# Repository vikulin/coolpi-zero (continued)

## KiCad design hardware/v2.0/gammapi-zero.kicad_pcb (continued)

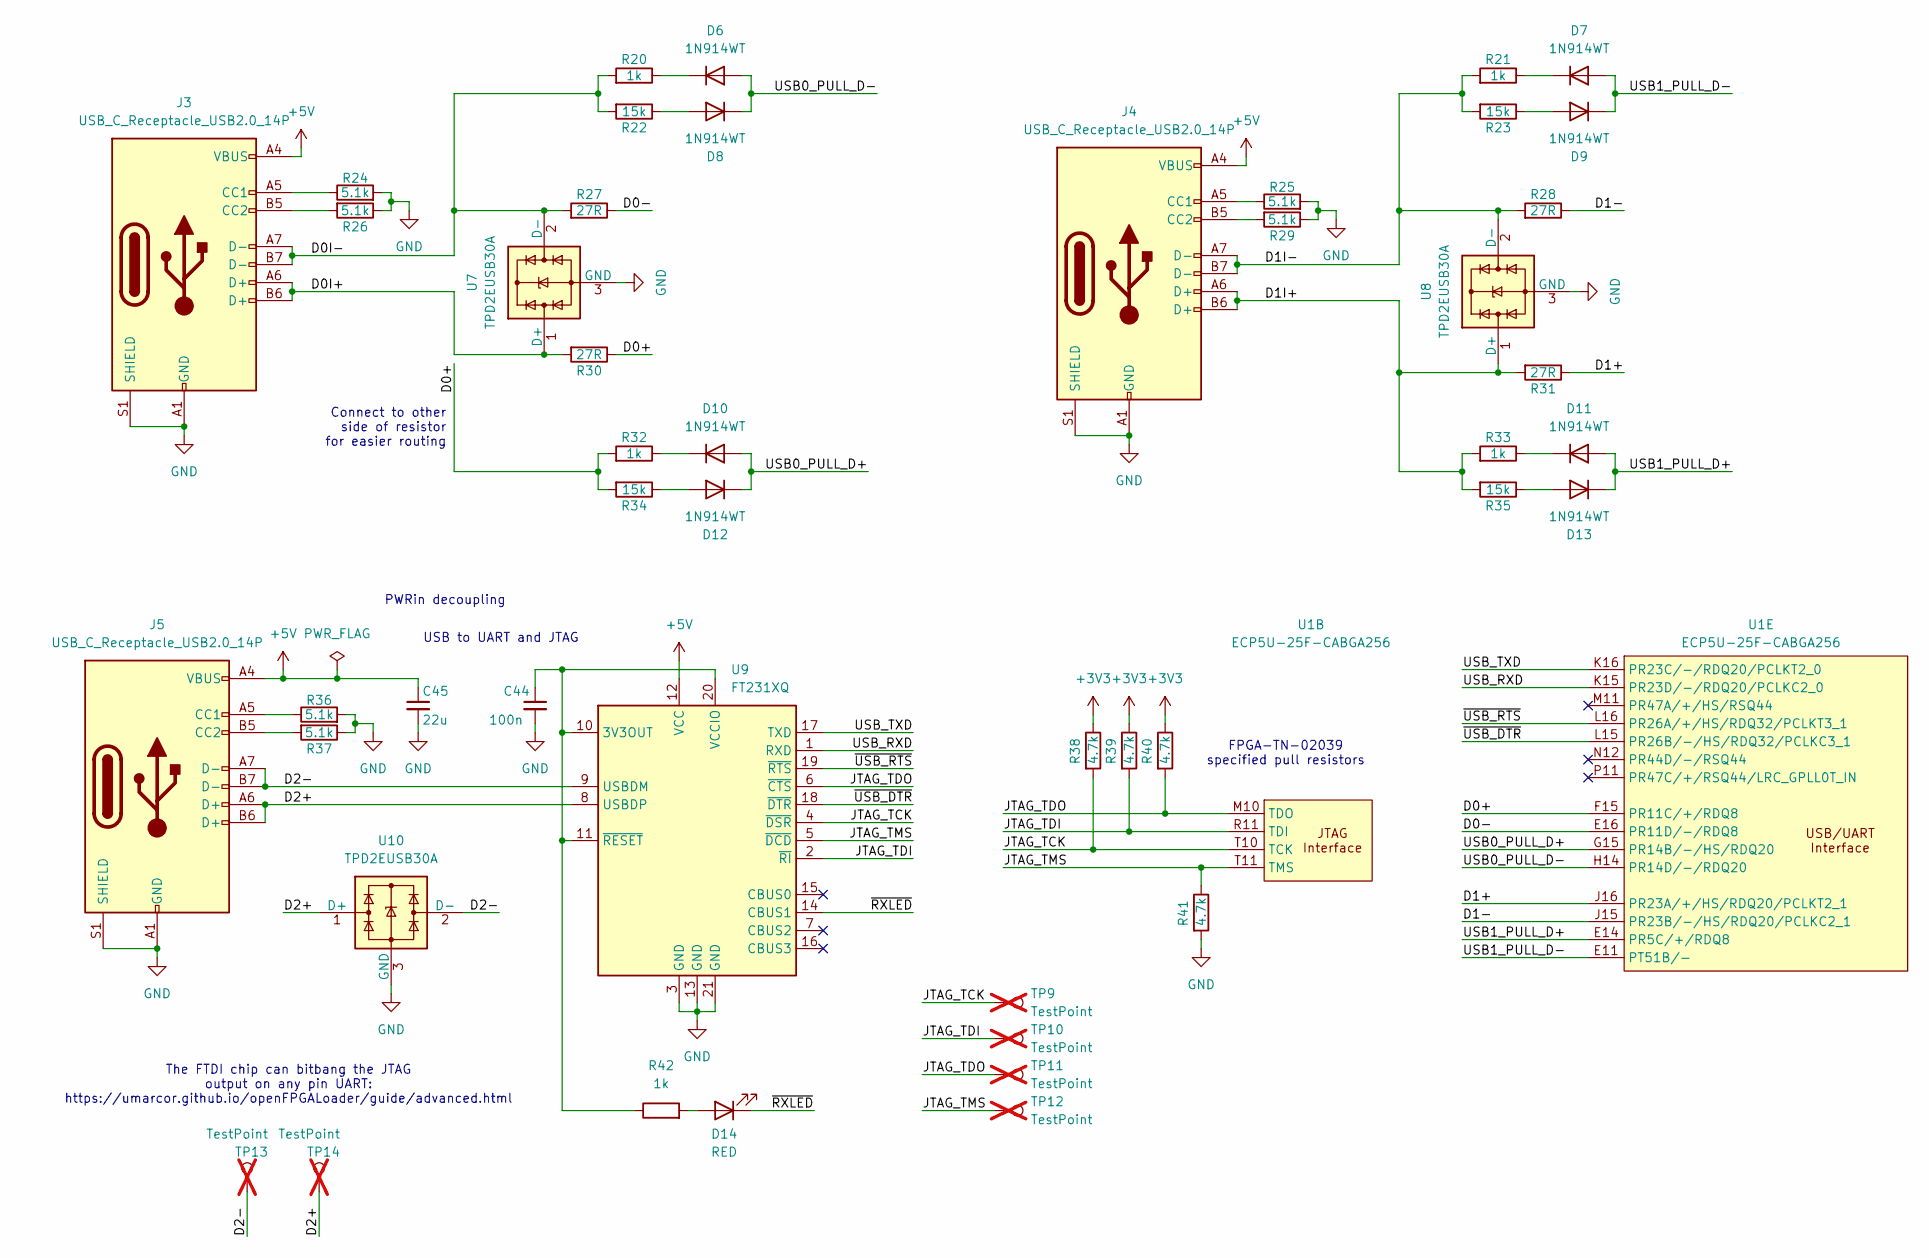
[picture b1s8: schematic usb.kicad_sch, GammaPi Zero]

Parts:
C44: 100n; C_0402_1005Metric; Manufactuer Part Number CL05B104KB54PNC; LCSC Part # C307331
C45: 22u; C_0603_1608Metric; Manufactuer Part Number CL10A226MQ8NRNC; LCSC Part # C59461
D6, D7, D8, D9, D10, D11, D12, D13: 1N914WT; D_SOD-523; Manufactuer Part Number 1N914WT; LCSC Part # C2836064
D14: RED; LED_0603_1608Metric; Manufactuer Part Number KT-0603R; LCSC Part # C2286
J3, J4, J5: USB_C_Receptacle_USB2.0_14P; USB_C_Receptacle_GCT_USB4105-xx-A_16P_TopMnt_Horizontal; Manufactuer Part Number TYPE-C 16PIN 2MD(073); LCSC Part # C2765186
R20, R21, R32, R33, R42: 1k; R_0402_1005Metric; Manufactuer Part Number 0402WGF1001TCE; LCSC Part # C11702
R22, R23, R34, R35: 15k; R_0402_1005Metric; Manufactuer Part Number 0402WGF1502TCE; LCSC Part # C25756
R24, R25, R26, R29, R36, R37: 5.1k; R_0402_1005Metric; Manufactuer Part Number 0402WGF5101TCE; LCSC Part # C25905
R27, R28, R30, R31: 27R; R_0201_0603Metric; Manufactuer Part Number 0201WMF270JTEE; LCSC Part # C473051
R38, R39, R40, R41: 4.7k; R_0402_1005Metric; Manufactuer Part Number 0402WGF4701TCE; LCSC Part # C25900
TP9, TP10, TP11, TP12: TestPoint; TestPoint_Pad_D1.0mm_Blank; not fitted
TP13, TP14: TestPoint; TestPoint_Pad_D2.0mm_Blank; not fitted
U1: ECP5U-25F-CABGA256; BGA-256_14.0x14.0mm_Layout16x16_P0.8mm_Ball0.45mm_Pad0.32mm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; MANUFACTURER_PART_NUMBER LFE5U-25F-6BG256C; LCSC Part # C1521614
U7, U8, U10: TPD2EUSB30A; Texas_DRT-3; Manufactuer Part Number TPD2EUSB30ADRTR; LCSC Part # C3011197
U9: FT231XQ; QFN-20-1EP_4x4mm_P0.5mm_EP2.5x2.5mm; Manufactuer Part Number FT231XQ-R; LCSC Part # C132159

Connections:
+3V3: R38.1, R39.1, R40.1; also elsewhere on the board
+5V: C45.1, J3.A4 (VBUS), J3.A9 (VBUS), J3.B4 (VBUS), J3.B9 (VBUS), J4.A4 (VBUS), J4.A9 (VBUS), J4.B4 (VBUS), J4.B9 (VBUS), J5.A4 (VBUS), J5.A9 (VBUS), J5.B4 (VBUS), J5.B9 (VBUS), U9.12 (VCC); also elsewhere on the board
/USB/D0+: R30.1, R32.2, R34.2, U1.F15 (PR11C/+/RDQ8)
/USB/D0-: R27.1, U1.E16 (PR11D/-/RDQ8)
/USB/D0I+: J3.A6 (D+), J3.B6 (D+), R30.2, U7.1 (D+)
/USB/D0I-: J3.A7 (D-), J3.B7 (D-), R20.2, R22.2, R27.2, U7.2 (D-)
/USB/D1+: R31.1, U1.J16 (PR23A/+/HS/RDQ20/PCLKT2_1)
/USB/D1-: R28.1, U1.J15 (PR23B/-/HS/RDQ20/PCLKC2_1)
/USB/D1I+: J4.A6 (D+), J4.B6 (D+), R31.2, R33.2, R35.2, U8.1 (D+)
/USB/D1I-: J4.A7 (D-), J4.B7 (D-), R21.2, R23.2, R28.2, U8.2 (D-)
/USB/D2+: J5.A6 (D+), J5.B6 (D+), TP14.1, U9.8 (USBDP), U10.1 (D+)
/USB/D2-: J5.A7 (D-), J5.B7 (D-), TP13.1, U9.9 (USBDM), U10.2 (D-)
/USB/JTAG_TCK: R38.2, TP9.1, U1.T10 (TCK), U9.4 (~DSR)
/USB/JTAG_TDI: R39.2, TP10.1, U1.R11 (TDI), U9.2 (~RI)
/USB/JTAG_TDO: R40.2, TP11.1, U1.M10 (TDO), U9.6 (~CTS)
/USB/JTAG_TMS: R41.1, TP12.1, U1.T11 (TMS), U9.5 (~DCD)
/USB/USB0_PULL_D+: D10.2 (A), D12.1 (K), U1.G15 (PR14B/-/HS/RDQ20)
/USB/USB0_PULL_D-: D6.2 (A), D8.1 (K), U1.H14 (PR14D/-/RDQ20)
/USB/USB1_PULL_D+: D11.2 (A), D13.1 (K), U1.E14 (PR5C/+/RDQ8)
/USB/USB1_PULL_D-: D7.2 (A), D9.1 (K), U1.E11 (PT51B/-)
/USB/USB_RXD: U1.K15 (PR23D/-/RDQ20/PCLKC2_0), U9.1 (RXD)
/USB/USB_TXD: U1.K16 (PR23C/-/RDQ20/PCLKT2_0), U9.17 (TXD)
/USB/~RXLED: D14.1 (K), U9.14 (CBUS1)
/USB/~USB_DTR: U1.L15 (PR26B/-/HS/RDQ32/PCLKC3_1), U9.18 (~DTR)
/USB/~USB_RTS: U1.L16 (PR26A/+/HS/RDQ32/PCLKT3_1), U9.19 (~RTS)
GND: C44.2, C45.2, J3.A1 (GND), J3.A12 (GND), J3.B1 (GND), J3.B12 (GND), J3.S1 (SHIELD), J4.A1 (GND), J4.A12 (GND), J4.B1 (GND), J4.B12 (GND), J4.S1 (SHIELD), J5.A1 (GND), J5.A12 (GND), J5.B1 (GND), J5.B12 (GND), J5.S1 (SHIELD), R24.2, R25.2, R26.1, R29.1, R36.2, R37.1, R41.2, U7.3 (GND), U8.3 (GND), U9.3 (GND), U9.13 (GND), U9.21 (GND), U10.3 (GND); also elsewhere on the board
unnamed: D6.1 (K), R20.1
unnamed: D7.1 (K), R21.1
unnamed: D8.2 (A), R22.1
unnamed: D9.2 (A), R23.1
unnamed: D10.1 (K), R32.1
unnamed: D11.1 (K), R33.1
unnamed: D12.2 (A), R34.1
unnamed: D13.2 (A), R35.1
unnamed: D14.2 (A), R42.2
unnamed: J3.A5 (CC1), R24.1
unnamed: J3.B5 (CC2), R26.2
unnamed: J4.A5 (CC1), R25.1
unnamed: J4.B5 (CC2), R29.2
unnamed: J5.A5 (CC1), R36.1
unnamed: J5.B5 (CC2), R37.2
unnamed: C44.1, R42.1, U9.10 (3V3OUT), U9.11 (~RESET), U9.20 (VCCIO)

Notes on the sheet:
PWRin decoupling
FPGA-TN-02039 specified pull resistors
USB to UART and JTAG
The FTDI chip can bitbang the JTAG output on any pin UART: https://umarcor.github.io/openFPGALoader/guide/advanced.html
Connect to other side of resistor for easier routing

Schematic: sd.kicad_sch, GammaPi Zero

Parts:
C54: 10u; C_0603_1608Metric; Manufactuer Part Number CL10A106KP8NNNC; LCSC Part # C19702
J6: Micro_SD_Card_Det2; microSD_HC_SOFNG_TF-008; Manufactuer Part Number TF-008; LCSC Part # C428465
U1: ECP5U-25F-CABGA256; BGA-256_14.0x14.0mm_Layout16x16_P0.8mm_Ball0.45mm_Pad0.32mm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; MANUFACTURER_PART_NUMBER LFE5U-25F-6BG256C; LCSC Part # C1521614

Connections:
+3V3: C54.1, J6.4 (VDD); also elsewhere on the board
/uSD/SD_CLK: J6.5 (CLK), U1.P15 (PR32B/-/HS/RDQSN32)
/uSD/SD_CMD: J6.3 (CMD), U1.N16 (PR32A/+/HS/RDQS32)
/uSD/SD_DAT0: J6.7 (DAT0), U1.P14 (PR38B/-/HS/RDQ44)
/uSD/SD_DAT1: J6.8 (DAT1), U1.R14 (PR41B/-/HS/RDQ44)
/uSD/SD_DAT2: J6.1 (DAT2), U1.M15 (PR26D/-/RDQ32/PCLKC3_0)
/uSD/SD_DAT3: J6.2 (DAT3/CD), U1.M14 (PR32D/-/RDQ32)
/uSD/SD_DET: J6.10 (DET_A), U1.M16 (PR26C/+/RDQ32/PCLKT3_0)
GND: C54.2, J6.6 (VSS), J6.9 (DET_B), J6.11 (SHIELD); also elsewhere on the board

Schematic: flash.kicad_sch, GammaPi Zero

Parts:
R43: 4.7k; R_0402_1005Metric; Manufactuer Part Number 0402WGF4701TCE; LCSC Part # C25900
R44, R45, R46, R47: 10k; R_0402_1005Metric; Manufactuer Part Number 0402WGF1002TCE; LCSC Part # C25744
R48, R49, R50: 15k; R_0402_1005Metric; Manufactuer Part Number 0402WGF1502TCE; LCSC Part # C25756
U1: ECP5U-25F-CABGA256; BGA-256_14.0x14.0mm_Layout16x16_P0.8mm_Ball0.45mm_Pad0.32mm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; MANUFACTURER_PART_NUMBER LFE5U-25F-6BG256C; LCSC Part # C1521614
U12: W25Q128JVS; SOIC-8_5.3x5.3mm_P1.27mm; Manufactuer Part Number W25Q128JVSIQ; LCSC Part # C97521

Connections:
+3V3: R43.1, R44.1, R45.1, R46.1, R47.1, R48.1, R49.1, R50.1, U1.P10 (CFG_1), U12.8 (VCC); also elsewhere on the board
/Flash/DONE: R49.2, U1.P9 (DONE)
/Flash/FLASH_CLK: U1.N9 (CCLK/MCLK/SCK), U12.6 (CLK)
/Flash/FLASH_MISO: R45.2, U1.T7 (PB11A/+/D1/MISO/IO1), U12.2 (DO/IO_{1})
/Flash/FLASH_MOSI: R44.2, U1.T8 (PB11B/-/D0/MOSI/IO0), U12.5 (DI/IO_{0})
/Flash/INITN: R50.2, U1.T9 (INITN)
/Flash/PROGRAMMING: R48.2, U1.R9 (PROGRAMN)
/Flash/~FLASH_CS: R43.2, U1.N8 (PB15A/+/HOLDN/DI/BUSY/CSSPIN/CEN), U12.1 (~CS)
/Flash/~FLASH_RESET: R47.2, U1.N7 (PL9A/+/D3/IO3), U12.7 (~HOLD/~RESET/IO_{3})
/Flash/~FLASH_WP: R46.2, U1.M7 (PL9B/-/D2/IO2), U12.3 (~WP/IO_{2})
GND: U1.N10 (CFG_0), U1.R10 (CPG_2), U12.4 (GND); also elsewhere on the board

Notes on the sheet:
128Mbit/16MiB
Special status pins Potentially add indicator LED Currently accesible via their resistor's pads
Pull up resistors from FPGA-TN-02039 CFG = 0b010 for MSPI mode

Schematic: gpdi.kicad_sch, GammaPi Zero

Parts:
C36, C37, C38, C39, C40, C41, C42, C43: 22n; C_0402_1005Metric; Manufactuer Part Number 0402B223K500NT; LCSC Part # C1532
D1: 3V6; D_SOD-323_HandSoldering; Manufactuer Part Number C19077438; LCSC Part # C19077438
J2: GPDI_C_1.3; XKB Connection A71-05H4-111N1; Manufactuer Part Number A71-05H4-111N1; LCSC Part # C2682170
R12, R14: 470R; R_0402_1005Metric; Manufactuer Part Number 0402WGF4700TCE; LCSC Part # C25117
R13: 10k; R_0402_1005Metric; Manufactuer Part Number 0402WGF1002TCE; LCSC Part # C25744
R15: 100k; R_0402_1005Metric; Manufactuer Part Number 0402WGF1003TCE; LCSC Part # C25741
R16, R17: 4.7k; R_0402_1005Metric; Manufactuer Part Number 0402WGF4701TCE; LCSC Part # C25900
R18, R19: 3.3k; R_0402_1005Metric; Manufactuer Part Number 0402WGF3301TCE; LCSC Part # C25890
U1: ECP5U-25F-CABGA256; BGA-256_14.0x14.0mm_Layout16x16_P0.8mm_Ball0.45mm_Pad0.32mm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; MANUFACTURER_PART_NUMBER LFE5U-25F-6BG256C; LCSC Part # C1521614
U6: PCA9306DC1; VSSOP-8_2.3x2mm_P0.5mm; Manufactuer Part Number PCA9306DC1; LCSC Part # C129510

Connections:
+3V3: R18.1, R19.1, U6.2 (VREF1); also elsewhere on the board
+5V: J2.18 (+5V), R15.1, R16.1, R17.1, U6.8 (EN); also elsewhere on the board
/GPDI/CONN_CK+: C42.2, J2.11 (CK+)
/GPDI/CONN_CK-: C43.2, J2.12 (CK-)
/GPDI/CONN_D0+: C40.2, J2.8 (D0+)
/GPDI/CONN_D0-: C41.2, J2.9 (D0-)
/GPDI/CONN_D1+: C38.2, J2.5 (D1+)
/GPDI/CONN_D1-: C39.2, J2.6 (D1-)
/GPDI/CONN_D2+: C36.2, J2.2 (D2+)
/GPDI/CONN_D2-: C37.2, J2.3 (D2-)
/GPDI/GPDI_CEC: R12.2, U1.R5 (PL44A/+/HS/LDQS44)
/GPDI/GPDI_CLK+: C42.1, U1.R12 (PR44A/+/HS/RDQS44)
/GPDI/GPDI_CLK-: C43.1, U1.T13 (PR44B/-/HS/RDQSN44)
/GPDI/GPDI_D0+: C40.1, U1.R13 (PR41C/+/RDQ44)
/GPDI/GPDI_D0-: C41.1, U1.T14 (PR41D/-/RSQ44)
/GPDI/GPDI_D1+: C38.1, U1.R15 (PR38C/+/RDQ44)
/GPDI/GPDI_D1-: C39.1, U1.T15 (PR38D/-/RDQ44)
/GPDI/GPDI_D2+: C36.1, U1.P16 (PR35A/+/HS/RDQ32)
/GPDI/GPDI_D2-: C37.1, U1.R16 (PR35B/-/HS/RDQ32/VREF1_3)
/GPDI/GPDI_HPD: D1.1 (K), R14.2, U1.L14 (PR32C/+/RDQ32)
/GPDI/GPDI_SCK_3V3: R19.2, U1.T3 (PL41D/-/LDQ44), U6.3 (SCL1)
/GPDI/GPDI_SCK_5V: J2.15 (SCL), R16.2, U6.6 (SCL2)
/GPDI/GPDI_SDA_3V3: R18.2, U1.T4 (PL44B/-/HS/LDQSN44), U6.4 (SDA1)
/GPDI/GPDI_SDA_5V: J2.16 (SDA), R17.2, U6.5 (SDA2)
/GPDI/GPDI_UTIL: R13.2, U1.P5 (PL47D/-/LDQ44/LLC_GPLL0C_IN)
GND: D1.2 (A), J2.1 (D2S), J2.4 (D1S), J2.7 (D0S), J2.10 (CKS), J2.13 (GND), J2.SH, U6.1 (GND); also elsewhere on the board
unnamed: J2.14 (CEC), R12.1
unnamed: J2.19 (HPD), R14.1
unnamed: J2.17 (UTILITY), R13.1
unnamed: R15.2, U6.7 (VREF2)

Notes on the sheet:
Shift 3v3 to 5v
3.6V zener on HPD line protects FPGA pin from HPD 5V
HDMI signals differential I/O pins
Signal filtering! UwU

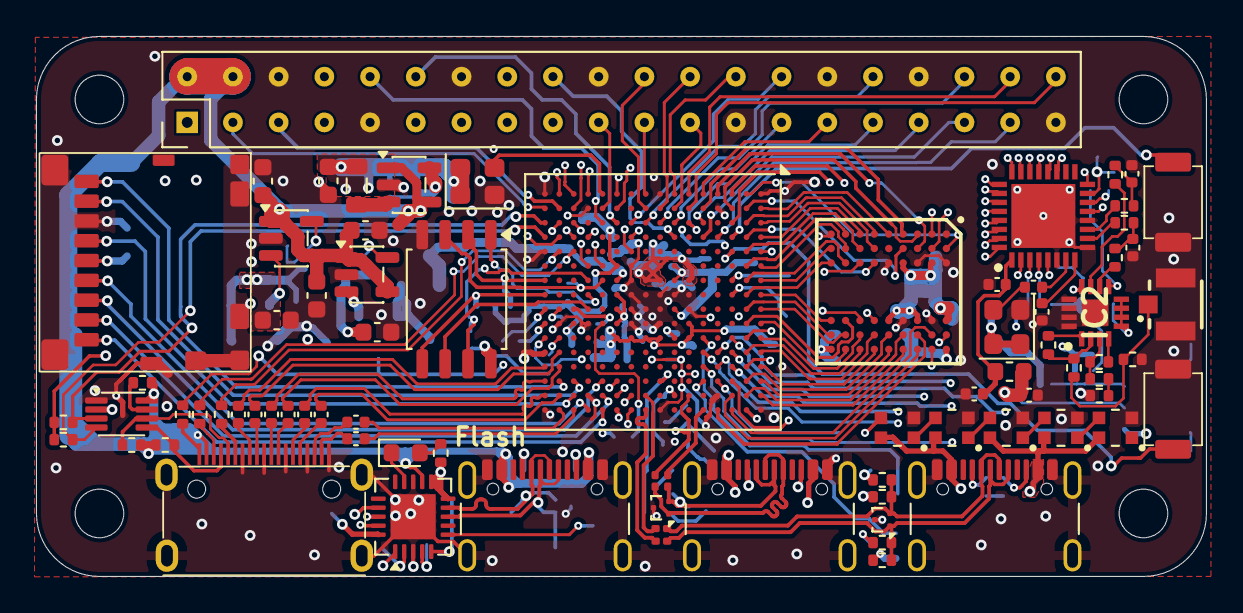
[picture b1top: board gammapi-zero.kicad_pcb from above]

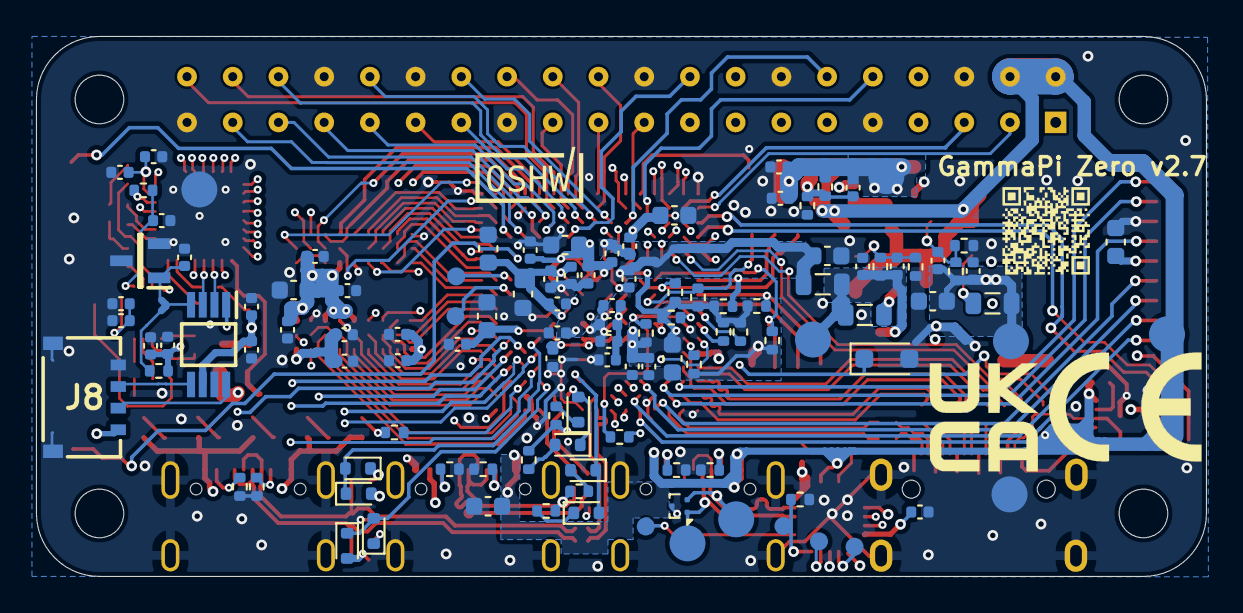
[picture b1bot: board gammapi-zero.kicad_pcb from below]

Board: 4 copper layers, 65.0 x 30.0 mm, 198 parts (115 on the bottom side), 209 nets.

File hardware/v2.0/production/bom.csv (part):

"Item #","*Designator","Qty","Manufacturer","*Mfg Part #","Description","Value","*Package/Footprint","DNP","Instructions/Notes"
"1","C1,C5,C6,C7,C8,C9,C10,C14,C16,C17,C20,C24,C25,C26,C27,C28,C29,C31,C32,C35,C44,C55,C61,C63,C64,C68,C69,C70,C71,C72,C73,C75,C76,C77,C82,C83","36","Samsung Electro-Mechanics","CL05B104KB54PNC","100nF ±10% 50V Ceramic Capacitor X7R 0402","100n","Capacitor_SMD:C_0402_1005Metric","",""
"2","C2,C3,C4,C15,C21,C22,C23,C30,C34,C53,C54,C62","12","Samsung Electro-Mechanics","CL10A106KP8NNNC","10uF ±10% 10V Ceramic Capacitor X5R 0603","10u","Capacitor_SMD:C_0603_1608Metric","",""
"3","C11,C13,C19,C33,C45","5","Samsung Electro-Mechanics","CL10A226MQ8NRNC","22uF ±20% 6.3V Ceramic Capacitor X5R 0603","22u","Capacitor_SMD:C_0603_1608Metric","",""
"4","C12","1","Samsung Electro-Mechanics","CL05B562KB5NNNC","5.6nF X7R ±10% 50V 0402 Ceramic Capacitors RoHS","5n6","Capacitor_SMD:C_0402_1005Metric","",""
"5","C18","1","Samsung Electro-Mechanics","CL05B272KB5NNNC","2.7nF ±10% 50V Ceramic Capacitor X7R 0402","2n7","Capacitor_SMD:C_0402_1005Metric","",""
"6","C36,C37,C38,C39,C40,C41,C42,C43,C46,C47,C48,C49,C50,C51,C52","15","FH","0402B223K500NT","22nF ±10% 50V Ceramic Capacitor X7R 0402","22n","Capacitor_SMD:C_0402_1005Metric","",""
"7","C56,C57","2","Samsung Electro-Mechanics","CL05C220JB5NNNC","22pF ±5% 50V Ceramic Capacitor C0G 0402","22p","Capacitor_SMD:C_0402_1005Metric","",""
"8","C58","1","Samsung Electro-Mechanics","CL05C6R8CB5NNNC","6.8pF 50V Ceramic Capacitor C0G 0402","6.8p","Capacitor_SMD:C_0402_1005Metric","",""
"9","C59,C60","2","Samsung Electro-Mechanics","CL05C390JB5NNNC","39pF ±5% 50V Ceramic Capacitor C0G 0402","39p","Capacitor_SMD:C_0402_1005Metric","",""
"10","C65","1","YAGEO","CC0402KRX5R6BB105","1uF ±10% 10V Ceramic Capacitor X5R 0402","1u","Capacitor_SMD:C_0402_1005Metric","",""
"11","C78,C84","2","muRata","GJM1555C1H1R3BB01D","1.3pF 50V Ceramic Capacitor C0G 0402","1p3","Capacitor_SMD:C_0402_1005Metric","",""
"12","C79,C80,C81","3","Samsung Electro-Mechanics","CL05B102KB5NNNC","1nF ±10% 50V Ceramic Capacitor X7R 0402","1n","Capacitor_SMD:C_0402_1005Metric","",""
"13","CB1","1","kinghelm","KHB(RG113)-55-29","IPEX to SMA Gen 1 Coaxial Cables (RF) Assemblies RoHS","KHB(RG113)-55-29","","DNP",""
"14","CB2","1","kinghelm","KHA(RG1.37)-TX50B-IPEX","IPEX to IPEX Gen 1 Coaxial Cables (RF) Assemblies RoHS","KHA(RG1.37)-TX50B-IPEX","","DNP",""
"15","D1","1","R+O","BZT52C3V6S","Zener Diode Independent 3.6V 200mW Surface Mount SOD-323","3V6","Diode_SMD:D_SOD-323_HandSoldering","",""
"16","D6,D7,D8,D9,D10,D11,D12,D13","8","CBI","1N914WT","75V 0.15A Fast switching Diode, SOD-523","1N914WT","Diode_SMD:D_SOD-523","",""
"17","D14","1","Hubei KENTO Elec","KT-0603R","Red 645nm LED Indication - Discrete 2.4V 0603","RED","LED_SMD:LED_0603_1608Metric","",""
"18","FB1","1","FH","CBG201209U101T","100Ω@100MHz 1 Line Ferrite Bead 0805 500mA 180mΩ","100R@100MHz","Inductor_SMD:L_0805_2012Metric","",""
"19","FB2","1","muRata","BLM18AG102SN1D","1kΩ@100MHz 1 Line Ferrite Bead 0603 450mA 500mΩ","1k@100MHz","Inductor_SMD:L_0603_1608Metric","",""
"20","IC1","1","ISSI","IS42S16160J-6BLI","DRAM 256M, 3.3V, SDRAM, 16Mx16, 166Mhz, 54 ball BGA (8mmx8mm) RoHS, IT","IS42S16160J-6BLI","BGA54C80P9X9_800X800X120","",""
"21","IC3","1","TI","LM4040AIM3-2.0/NOPB","100-ppm/C precision micropower shunt voltage reference","LM4040AIM3-2.0_NOPB","SOT95P237X95-3N","",""
"22","IC4","1","ADI","LTC2622IMS8#PBF","Linear Technology LTC2622IMS8#PBF, 2-channel 12 bit Serial DAC, 50MHz, 8-Pin MSOP","LTC2622IMS8#PBF","SOP65P490X110-8N","",""
"23","IC5","1","ADI","LTC6409IUDB#TRPBF","High Speed Operational Amplifiers 10GHz GBW, 1.1nV/vHz Diff Amp/ADC Drvr , 2.7V ~ 5.25V , 52mA , -40C ~ +85C","LTC6409IUDB#TRPBF","LTC6409IUDBTRPBF","",""
"24","IC6","1","TI","ADS6122IRHBT","12-Bit, 65-MSPS Analog-to-Digital Converter (ADC)","ADS6122IRHBT","QFN50P500X500X100-33N-D","",""
"25","J2","1","XKB Connection","A71-05H4-111N1","GPDI type C connector","GPDI_C_1.3","icepi-lib:XKB Connection A71-05H4-111N1","",""
"26","J3,J4,J5","3","SHOU HAN","TYPE-C 16PIN 2MD(073)","USB 2.0-only 14P Type-C Receptacle connector","USB_C_Receptacle_USB2.0_14P","Connector_USB:USB_C_Receptacle_GCT_USB4105-xx-A_16P_TopMnt_Horizontal","",""
"27","J6","1","SOFNG","TF-008","Micro SD Card Socket with two card detection pins","Micro_SD_Card_Det2","icepi-lib:microSD_HC_SOFNG_TF-008","",""
"28","J8","1","JST Commercial","M04B-ACHSS-A-GAN-TF(LF)(SN)","CONN HEADER SMD R/A 4POS 1.2MM","BM04B-ACHSS-A-GAN-TF_LF__SN_","BM04BACHSSAGANTFLFSN","",""
"29","L1,L2,L3","3","TDK","MLP2012S2R2MT0S1","800mA 2.2uH 299mΩ Multilayer inductor ±20% 0805 Fixed Inductors RoHS","2.2uH","Inductor_SMD:L_0805_2012Metric","",""
"30","LED1,LED2,LED3,LED4,LED5","5","Inolux","IN-PI15TAT5R5G5B","SMD-4_1.5X1.5 LED Addressable, Specialty RoHS","IN-PI15TAT5R5G5B","INPI15TAT5R5G5B","",""
"31","R1","1","UNI-ROYAL","0402WGF5490TCE","549Ω ±1% 62.5mW 0402 Thick Film Resistor","549R","Resistor_SMD:R_0402_1005Metric","",""
"32","R2","1","UNI-ROYAL","0402WGF1000TCE","100Ω ±1% 62.5mW 0402 Thick Film Resistor","100R","Resistor_SMD:R_0402_1005Metric","",""
"33","R3,R4","2","UNI-ROYAL","0402WGF100JTCE","10Ω ±1% 62.5mW 0402 Thick Film Resistor","10R","Resistor_SMD:R_0402_1005Metric","",""
"34","R5,R51","2","UNI-ROYAL","0402WGF332JTCE","33.2Ω ±1% 62.5mW 0402 Thick Film Resistor","33R2","Resistor_SMD:R_0402_1005Metric","",""
"35","R6","1","UNI-ROYAL","0402WGF2553TCE","255kΩ ±1% 62.5mW 0402 Thick Film Resistor","255k","Resistor_SMD:R_0402_1005Metric","",""
"36","R7","1","UNI-ROYAL","0402WGF3013TCE","301kΩ ±1% 62.5mW 0402 Thick Film Resistor","301k","Resistor_SMD:R_0402_1005Metric","",""
"37","R8","1","UNI-ROYAL","0402WGF8873TCE","887kΩ ±1% 62.5mW 0402 Thick Film Resistor","887k","Resistor_SMD:R_0402_1005Metric","",""
"38","R9","1","UNI-ROYAL","0402WGF2803TCE","280kΩ ±1% 62.5mW 0402 Thick Film Resistor","280k","Resistor_SMD:R_0402_1005Metric","",""
"39","R10","1","UNI-ROYAL","0402WGF4533TCE","453kΩ ±1% 62.5mW 0402 Thick Film Resistor","453k","Resistor_SMD:R_0402_1005Metric","",""
"40","R11,R15,R55","3","UNI-ROYAL","0402WGF1003TCE","100kΩ ±1% 62.5mW 0402 Thick Film Resistor","100k","Resistor_SMD:R_0402_1005Metric","",""
"41","R12,R14","2","UNI-ROYAL","0402WGF4700TCE","470Ω ±1% 62.5mW 0402 Thick Film Resistor","470R","Resistor_SMD:R_0402_1005Metric","",""
"42","R13,R44,R45,R46,R47","5","UNI-ROYAL","0402WGF1002TCE","10kΩ ±1% 62.5mW 0402 Thick Film Resistor","10k","Resistor_SMD:R_0402_1005Metric","",""
"43","R16,R17,R38,R39,R40,R41,R43","7","UNI-ROYAL","0402WGF4701TCE","4.7kΩ ±1% 62.5mW 0402 Thick Film Resistor","4.7k","Resistor_SMD:R_0402_1005Metric","",""
"44","R18,R19","2","UNI-ROYAL","0402WGF3301TCE","3.3kΩ ±1% 62.5mW 0402 Thick Film Resistor","3.3k","Resistor_SMD:R_0402_1005Metric","",""
"45","R20,R21,R32,R33,R42","5","UNI-ROYAL","0402WGF1001TCE","1kΩ ±1% 62.5mW 0402 Thick Film Resistor","1k","Resistor_SMD:R_0402_1005Metric","",""
"46","R22,R23,R34,R35,R48,R49,R50","7","UNI-ROYAL","0402WGF1502TCE","15kΩ ±1% 62.5mW 0402 Thick Film Resistor","15k","Resistor_SMD:R_0402_1005Metric","",""
"47","R24,R25,R26,R29,R36,R37","6","UNI-ROYAL","0402WGF5101TCE","5.1kΩ ±1% 62.5mW 0402 Thick Film Resistor","5.1k","Resistor_SMD:R_0402_1005Metric","",""
"48","R27,R28,R30,R31","4","UNI-ROYAL","0201WMF270JTEE","27Ω ±1% 50mW 0201 Thick Film Resistor","27R","Resistor_SMD:R_0201_0603Metric","",""
"49","R52,R57,R60,R61","4","PANASONIC","ERA2AEB151X","150Ω ±0.1% 63mW 0402 Thin Film Resistor AEC-Q200","150R","Resistor_SMD:R_0402_1005Metric","",""
"50","R53,R54","2","UNI-ROYAL","0402WGF4704TCE","4.7MΩ ±1% 62.5mW 0402 Thick Film Resistor","4M7","Resistor_SMD:R_0402_1005Metric","",""
"51","R58","1","UNI-ROYAL","0402WGF1301TCE","1.3kΩ ±1% 62.5mW 0402 Thick Film Resistor","1k3","Resistor_SMD:R_0402_1005Metric","",""
"52","R59","1","UNI-ROYAL","RC0402FR-0766R5L","66.5Ω 62.5mW 50V Thick Film Resistor ±100ppm/℃ ±1% 0402 Chip Resistor - Surface Mount RoHS","66R5","Resistor_SMD:R_0402_1005Metric","",""
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
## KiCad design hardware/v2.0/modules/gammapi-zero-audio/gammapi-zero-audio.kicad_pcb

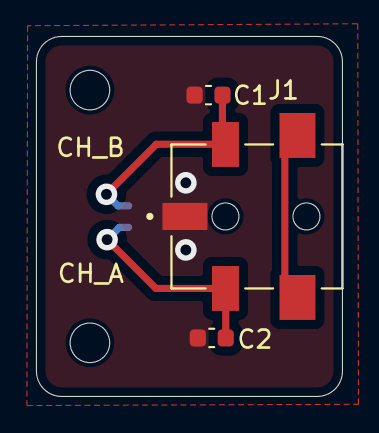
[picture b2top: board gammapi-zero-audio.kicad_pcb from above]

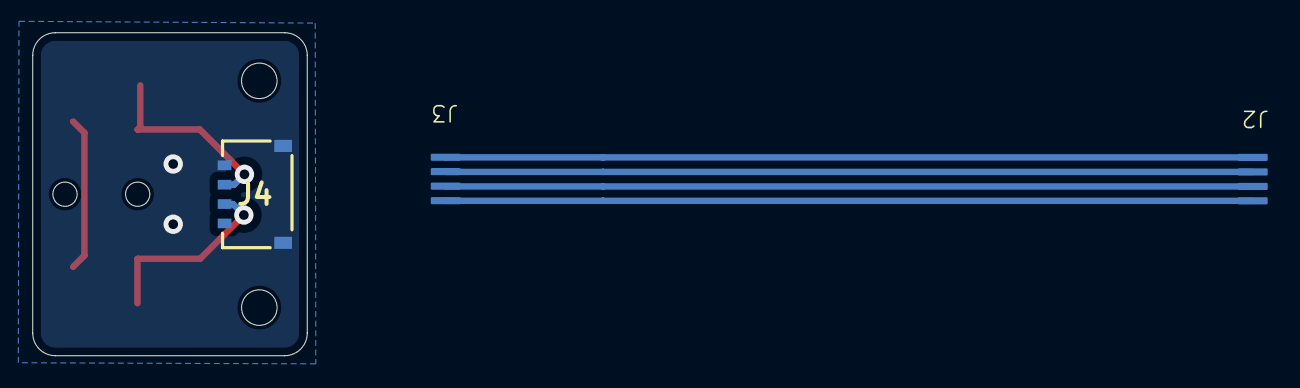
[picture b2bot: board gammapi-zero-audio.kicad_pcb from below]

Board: 2 copper layers, 17.0 x 20.0 mm, 6 parts (3 on the bottom side), 8 nets.

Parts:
C1, C2: 1n; C_0603_1608Metric
J1: SJ1-42534-SMT-TR; CUI_SJ1-42534-SMT-TR
J2, J3: ACHR-04V-A-S
J4: BM04B-ACHSS-A-GAN-TF_LF__SN_; BM04BACHSSAGANTFLFSN

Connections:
+3V3: J2.1, J3.4
/CH_A: J2.2, J3.3
/CH_B: J2.3, J3.2
GND1: J2.4, J3.1
GND2: C1.2, C2.2, J1.1, J4.1, J4.MP1, J4.MP2
unnamed: C1.1, J1.2, J4.2
unnamed: C2.1, J1.3, J4.3
unnamed: J1.4_1, J1.4_2

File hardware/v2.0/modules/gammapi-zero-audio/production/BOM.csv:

"Item #","*Designator","Qty","Manufacturer","*Mfg Part #","Description","Value","*Package/Footprint","DNP","Instructions/Notes"
"1","C1,C2","2","Samsung Electro-Mechanics","CL10B102KB8NNNC","1nF ±10% 50V Ceramic Capacitor X7R 0603","1n","Capacitor_SMD:C_0603_1608Metric","",""
"2","CB1","1","TRIUMPH CABLE","UL1571#32AWG Purple","Single Conductor Cables (Hook-Up Wire) RoHS","32AWG Red 5cm","","DNP",""
"3","CB2","1","TRIUMPH CABLE","UL10064#32AWG Grey","Single Conductor Cables (Hook-Up Wire) RoHS","32AWG White 5cm","","DNP",""
"4","CB3","1","TRIUMPH CABLE","UL10064#32AWG Green","Single Conductor Cables (Hook-Up Wire) RoHS","32AWG Green 5cm","","DNP",""
"5","CB4","1","TRIUMPH CABLE","UL10064#32AWG Black","Single Conductor Cables (Hook-Up Wire) RoHS","32AWG Black 5cm","","DNP",""
"6","J1","1","CUI Devices","SJ1-42534-SMT-TR","2.50mm (0.094"", 3/32"", Sub Mini, Miniature) - Headphone Phone Jack Stereo (4 Conductor, TRRS) Connector Solder","SJ1-42534-SMT-TR","SJ1_42534_SMT_TR:CUI_SJ1-42534-SMT-TR","",""
"7","J2,J3","2","JST","ACHR-04V-A-S","4 Rectangular Connectors - Housings Receptacle Natural 0.047{dblquote} (1.20mm)","ACHR-04V-A-S","ACHR-04V-A-S:ACHR-04V-A-S","DNP",""
"8","J4","1","JST","BM04B-ACHSS-A-GAN-TF(LF)(SN)","CONN HEADER SMD R/A 4POS 1.2MM","BM04B-ACHSS-A-GAN-TF_LF__SN_","BM04BACHSSAGANTFLFSN","",""
"9","T1,T2,T3,T4,T5,T6,T7,T8","8","JST","SACH-003G-P0.2B","Connector Terminal ACH Gold 30~32 AWG Crimp","SACH-003G-P0.2B","","DNP","Use crimping machine AP-K2N"

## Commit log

2026-01-02 Replaced memory AS4C16M16SA 54-TFBGA (8x8)
2026-01-02 Removed LEDs D3, D4, D5
2026-01-02 Added vias
2026-01-03 Connected traces to memory
2026-01-03 1.1V net capacitors
2026-01-03 2.5V LDO
2026-01-03 3.3V LDO
2026-01-03 3.3V memory fix
2026-01-03 HDMI preparation
2026-01-04 HDMI preparation, memory traces fix
2026-01-04 GND fix
2026-01-04 HDMI complete
2026-01-08 Initial plan for adding an external ADC
2026-01-08 ADC diff pair
2026-01-10 Minor changes
2026-01-12 Replaced 2.5 and 1.1V regulators with single LTC3407A-2
2026-01-12 DRC fixes
2026-01-13 Revise contact details in README
    Updated contact information for inquiries.
2026-01-15 LDOs dividers update
2026-01-17 ADC 6 diff lines
2026-01-17 Routs updates
2026-01-17 ADC lines
2026-01-18 ADC CLKOUT±
2026-01-18 Power line fixes
2026-01-18 LEDs closer positioning
2026-01-18 DRC almost pass
2026-01-19 ADC power
2026-01-19 LEDs update for IC
2026-01-20 ADC driver enable pin
2026-01-20 ADC driver adjustment
2026-01-20 ADC SPI
2026-01-20 ADC input driver power
2026-01-20 ADC sense
2026-01-21 ADC SPI SDO
2026-01-21 ADC SPI SDO pull up
2026-01-22 HPD line protection
2026-01-23 ADC driver power and signal input
2026-01-23 Pads clearance fix
2026-01-23 BOM fields unification for PCBWay requirements
2026-01-24 ADC datasheet compliance
2026-01-24 Grouped FPGA, ADC, ADC Driver, LEDs IC
2026-01-24 1V1 connection issue fix
2026-01-25 External ADC finalization
2026-01-25 Clock label fix
2026-01-25 Minor fixes
2026-01-25 ADC driver power pins bypass
2026-01-25 Rebranding Icepi Zero to GammaPi Zero in README
2026-01-25 Fix typo in GammaPi Zero description
2026-01-25 Update Acorn Atom image in README
2026-01-25 QR code update
2026-01-25 Repo links update
2026-01-25 BOM updated, Update README.md
2026-01-26 Extra CS for SPI
2026-01-26 LTC2630 DAC
2026-01-26 DAC Vout
2026-01-26 Logo fix
2026-01-26 ERC pass
2026-01-26 BOM update
2026-01-26 Label fixes
2026-01-27 2CH DAC
2026-01-27 DRC pass
2026-01-27 6-layers
2026-01-27 ADC line
2026-01-27 5V power layer
2026-01-29 Impedance control 100Ohm ADC LVDS diff pairs
    Calculated for PCBWay 92th stack with 1OZ inner copper layer
2026-01-29 DAC voltage reference
2026-01-29 Components description update
2026-01-30 LTC6409 ADC driver
2026-01-30 Prod ADC
2026-01-30 Prod ADC input
2026-01-31 Prod ADC power line
2026-01-31 Label update
2026-02-01 Coaxial cables
2026-02-01 Goodbye Icepi
2026-02-02 Audio module
2026-02-06 Layout fixes
2026-02-08 Layout adjustments
2026-02-08 ADC digital line power fix
2026-02-28 JLCPCB profile
2026-03-01 ADA4932-1 amplifier
    ADA4932-1 amplifier replaced LTC6409
2026-03-01 J8 DAC output connector update
2026-03-02 TLV62569DBVR Voltage Regulator
2026-03-02 WS2812B-2020 LED Update
2026-03-02 Capacitor update
2026-03-03 Unified vias with 0.2/0.45mm dimensions
2026-03-03 Pad adjustments
2026-03-03 Bump version
2026-03-11 Update ADC speed from 25 MBPS to 50 MBPS
